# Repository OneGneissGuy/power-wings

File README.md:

# power-wings : A collection of Adafruit FeatherWing based power supplies 

All boards are designed in Kicad 5.1x

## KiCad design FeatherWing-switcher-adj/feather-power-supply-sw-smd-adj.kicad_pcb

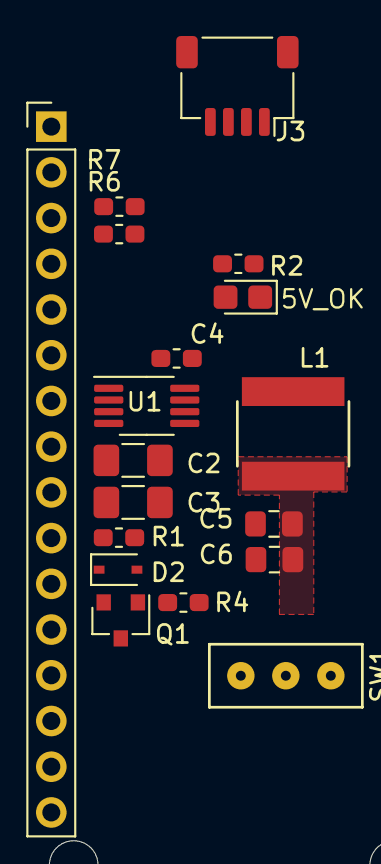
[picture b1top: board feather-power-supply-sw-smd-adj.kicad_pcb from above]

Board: 2 copper layers, 21 parts (0 on the bottom side), 10 nets, no tracks yet.

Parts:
C2, C3: 10uF; C_1206_3216Metric_Pad1.42x1.75mm_HandSolder
C4: 1uF; C_0603_1608Metric_Pad1.05x0.95mm_HandSolder
C5, C6: 10uF; C_0805_2012Metric_Pad1.15x1.40mm_HandSolder
D2: 10V; D_SOD-323
D3: 5V_OK; LED_0805_2012Metric_Castellated
H3, H4: MountingHole; MountingHole_2.7mm_M2.5
J2: Conn_01x16; PinHeader_1x16_P2.54mm_Vertical
J3: QWIIC; JST_SH_SM04B-SRSS-TB_1x04-1MP_P1.00mm_Horizontal
J4: 0.1; PinHeader_1x04_P2.54mm_Vertical
L1: 27uH; ASPI-6045S-270
Q1: Q_PMOS_GSD; SOT-23
R1, R6: 1M; R_0603_1608Metric_Pad1.05x0.95mm_HandSolder
R2: 330; R_0603_1608Metric_Pad1.05x0.95mm_HandSolder
R4: 10K; R_0603_1608Metric_Pad1.05x0.95mm_HandSolder
R7: 100K; R_0603_1608Metric_Pad1.05x0.95mm_HandSolder
SW1: SW_SPDT; sw-spdt-DIYhz
U1: MCP16312MS; MSOP-8_3x3mm_P0.65mm

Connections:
+5.3V: C5.1, C6.1, L1.2
+5V: J3.2, R2.1
A1: J2.6, R6.2, R7.1
GND: C2.2, C3.2, C4.2, C5.2, C6.2, D3.1, J2.4, J3.1, R4.2, R7.2, U1.5, U1.8
unnamed: L1.1, U1.6
unnamed: C4.1, U1.2
unnamed: D2.2, Q1.1, R4.1
unnamed: D3.2, R2.2
unnamed: R1.2, U1.3
VIN_SW: C2.1, C3.1, D2.1, Q1.2, R1.1, U1.4

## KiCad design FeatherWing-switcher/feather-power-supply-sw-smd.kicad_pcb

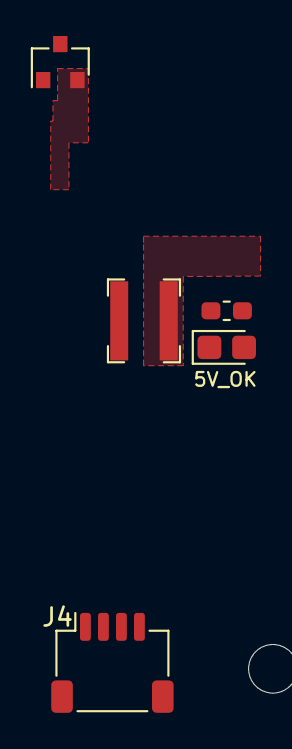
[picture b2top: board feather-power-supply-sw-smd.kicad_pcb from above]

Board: 2 copper layers, 8 parts (0 on the bottom side), 3 nets, no tracks yet.

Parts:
D2: 5V_OK; LED_0805_2012Metric_Castellated
H3, H4: MountingHole; MountingHole_2.7mm_M2.5
J4: QWIIC; JST_SH_SM04B-SRSS-TB_1x04-1MP_P1.00mm_Horizontal
J5: 0.1; PinHeader_1x04_P2.54mm_Vertical
L1: 4.7uH; TDK-VLS4012HBX
Q1: Q_PMOS_GSD; SOT-23
R5: 1k; R_0603_1608Metric_Pad1.05x0.95mm_HandSolder

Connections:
+5V: J4.2, L1.2, R5.1
GND: D2.1, J4.1, Q1.1
unnamed: D2.2, R5.2

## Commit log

2020-09-02 init commit
2020-09-02 adds readme
2020-09-02 updates sw board folder name
2020-09-02 updates sch title block, adds render
2020-09-02 adds oshw logo; fixes a0 pin ref
2020-09-02 rename schematic
2020-09-02 update mounting holes
2020-09-02 add license
2020-09-06 adds qwicc conn
2020-09-06 update render file
2020-09-17 adds proto and leds
2020-09-21 major updates to route buses using copper pours
2020-09-21 update pdf schematic
2020-09-21 minor bom consolidation
2020-09-21 reduce ground pour clearance
2020-09-21 updates pad clearance and bom
2020-09-21 updates gerbers for fab
2020-09-23 clean up schematic and bump to v1.1
2020-10-06 v1.0 schematic cleanup
2020-10-06 update board to version 2
2020-10-06 updates boms and render to v2
2020-10-12 clean up sw smd files
2020-10-12 add a featherwing adj board
2020-10-12 update routing with cu pours
2020-10-12 minor board changes
2020-10-12 minor board/schematic changes
2020-10-21 minor updates to bom and layout
2020-10-21 update fb res val and inductor val
2020-10-21 generate boms
2020-10-21 update inductor and boms
2020-10-23 plots updated schematic
2020-10-23 fixes vusb/vbus pin number
2020-10-24 generates ibom
2020-10-24 fixes 5V bodge and connects vdivider
2020-10-24 v2 fixes
2020-10-24 adds input switch
2020-10-24 adds led jp
2020-10-24 updates sch version
2020-10-25 v2.1 fix vsense wiring and update layout
